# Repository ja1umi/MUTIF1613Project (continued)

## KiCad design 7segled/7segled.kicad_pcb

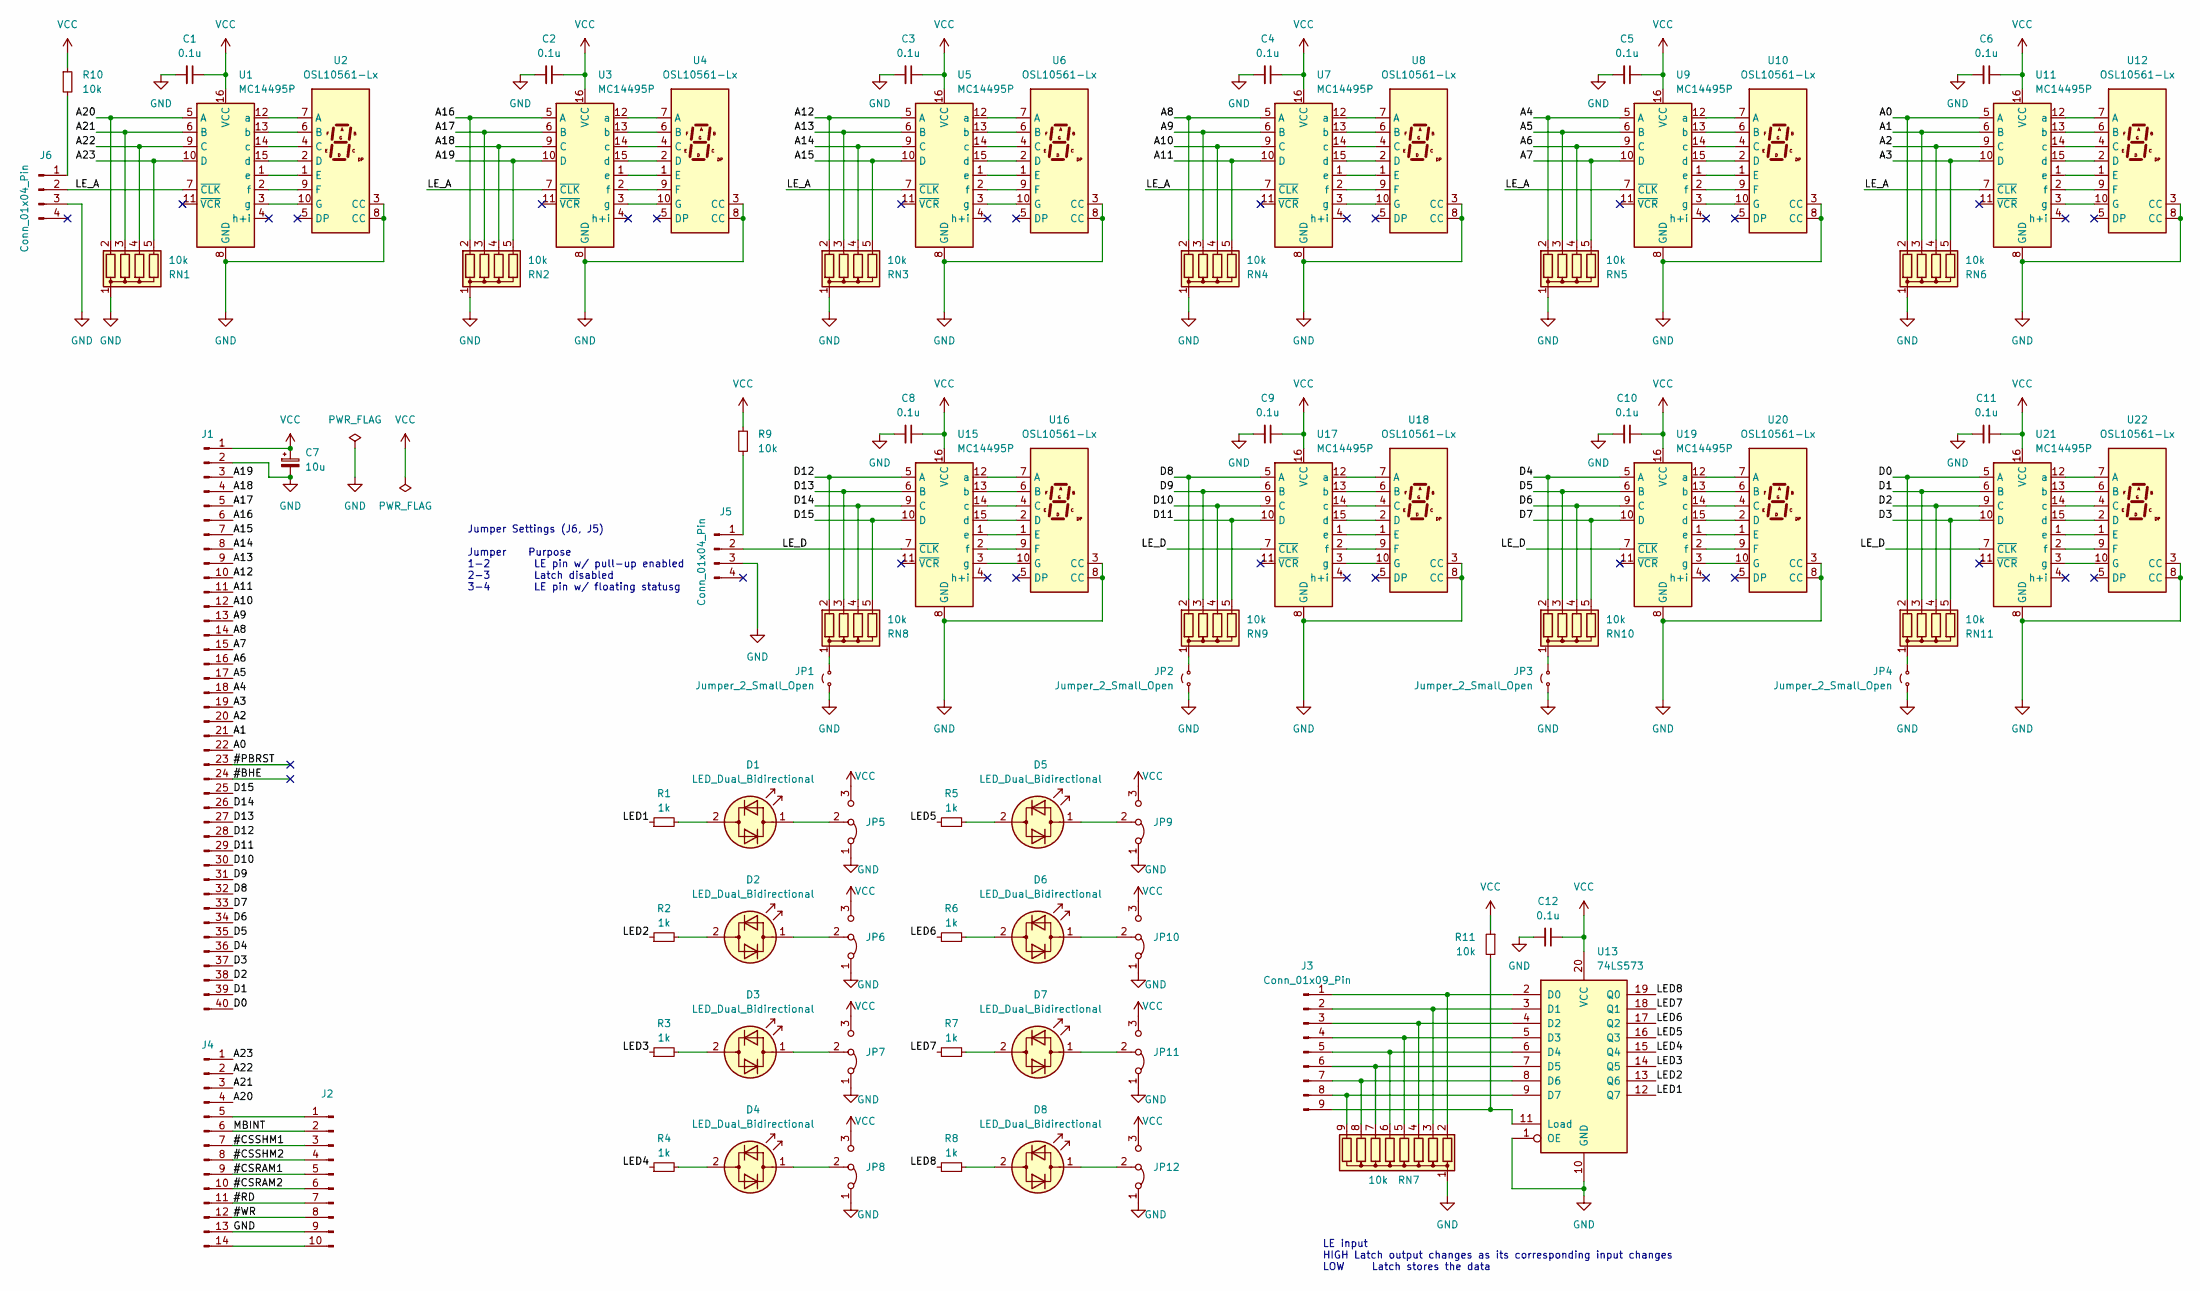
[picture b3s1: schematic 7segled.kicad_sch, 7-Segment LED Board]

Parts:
C1, C2, C3, C4, C5, C6, C8, C9, C10, C11, C12: 0.1u; C_Disc_D5.0mm_W2.5mm_P5.00mm
C7: 10u; CP_Radial_D5.0mm_P2.50mm
D1, D2, D3, D4, D5, D6, D7, D8: LED_Dual_Bidirectional; LED_D5.0mm
J1: Conn_01x40_Pin; PinHeader_1x40_P2.54mm_Vertical
J2: Conn_01x10_Pin; PinHeader_1x10_P2.54mm_Vertical
J3: Conn_01x09_Pin; PinHeader_1x09_P2.54mm_Vertical
J4: Conn_01x14_Pin; PinHeader_1x14_P2.54mm_Vertical
J5, J6: Conn_01x04_Pin; PinHeader_1x04_P2.54mm_Vertical
JP1, JP2, JP3, JP4: Jumper_2_Small_Open; PinHeader_1x02_P2.54mm_Vertical
JP5, JP6, JP7, JP8, JP9, JP10, JP11, JP12: Jumper_3_Bridged12; PinHeader_1x03_P2.54mm_Vertical
R1, R2, R3, R4, R5, R6, R7, R8: 1k; R_Axial_DIN0207_L6.3mm_D2.5mm_P7.62mm_Horizontal
R9, R10, R11: 10k; R_Axial_DIN0207_L6.3mm_D2.5mm_P7.62mm_Horizontal
RN1, RN2, RN3, RN4, RN5, RN6, RN8, RN9, RN10, RN11: 10k; R_Array_SIP5
RN7: 10k; R_Array_SIP9
U1, U3, U5, U7, U9, U11, U15, U17, U19, U21: MC14495P; DIP-16_W7.62mm_LongPads
U2, U4, U6, U8, U10, U12, U16, U18, U20, U22: OSL10561-Lx; D1X8K
U13: 74LS573; DIP-20_W7.62mm_LongPads

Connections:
/#BHE: J1.24
/#CSRAM1: J2.5, J4.9
/#CSRAM2: J2.6, J4.10
/#CSSHM1: J2.3, J4.7
/#CSSHM2: J2.4, J4.8
/#PBRST: J1.23
/#RD: J2.7, J4.11
/#WR: J2.8, J4.12
/A0: J1.22, RN6.2 (R1), U11.5 (A)
/A1: J1.21, RN6.3 (R2), U11.6 (B)
/A2: J1.20, RN6.4 (R3), U11.9 (C)
/A3: J1.19, RN6.5 (R4), U11.10 (D)
/A4: J1.18, RN5.2 (R1), U9.5 (A)
/A5: J1.17, RN5.3 (R2), U9.6 (B)
/A6: J1.16, RN5.4 (R3), U9.9 (C)
/A7: J1.15, RN5.5 (R4), U9.10 (D)
/A8: J1.14, RN4.2 (R1), U7.5 (A)
/A9: J1.13, RN4.3 (R2), U7.6 (B)
/A10: J1.12, RN4.4 (R3), U7.9 (C)
/A11: J1.11, RN4.5 (R4), U7.10 (D)
/A12: J1.10, RN3.2 (R1), U5.5 (A)
/A13: J1.9, RN3.3 (R2), U5.6 (B)
/A14: J1.8, RN3.4 (R3), U5.9 (C)
/A15: J1.7, RN3.5 (R4), U5.10 (D)
/A16: J1.6, RN2.2 (R1), U3.5 (A)
/A17: J1.5, RN2.3 (R2), U3.6 (B)
/A18: J1.4, RN2.4 (R3), U3.9 (C)
/A19: J1.3, RN2.5 (R4), U3.10 (D)
/A20: J4.4, RN1.2 (R1), U1.5 (A)
/A21: J4.3, RN1.3 (R2), U1.6 (B)
/A22: J4.2, RN1.4 (R3), U1.9 (C)
/A23: J4.1, RN1.5 (R4), U1.10 (D)
/D0: J1.40, RN11.2 (R1), U21.5 (A)
/D1: J1.39, RN11.3 (R2), U21.6 (B)
/D2: J1.38, RN11.4 (R3), U21.9 (C)
/D3: J1.37, RN11.5 (R4), U21.10 (D)
/D4: J1.36, RN10.2 (R1), U19.5 (A)
/D5: J1.35, RN10.3 (R2), U19.6 (B)
/D6: J1.34, RN10.4 (R3), U19.9 (C)
/D7: J1.33, RN10.5 (R4), U19.10 (D)
/D8: J1.32, RN9.2 (R1), U17.5 (A)
/D9: J1.31, RN9.3 (R2), U17.6 (B)
/D10: J1.30, RN9.4 (R3), U17.9 (C)
/D11: J1.29, RN9.5 (R4), U17.10 (D)
/D12: J1.28, RN8.2 (R1), U15.5 (A)
/D13: J1.27, RN8.3 (R2), U15.6 (B)
/D14: J1.26, RN8.4 (R3), U15.9 (C)
/D15: J1.25, RN8.5 (R4), U15.10 (D)
/LED1: R1.1, U13.12 (Q7)
/LED2: R2.1, U13.13 (Q6)
/LED3: R3.1, U13.14 (Q5)
/LED4: R4.1, U13.15 (Q4)
/LED5: R5.1, U13.16 (Q3)
/LED6: R6.1, U13.17 (Q2)
/LED7: R7.1, U13.18 (Q1)
/LED8: R8.1, U13.19 (Q0)
/LE_A: J6.2, U1.7 (~CLK), U3.7 (~CLK), U5.7 (~CLK), U7.7 (~CLK), U9.7 (~CLK), U11.7 (~CLK)
/LE_D: J5.2, U15.7 (~CLK), U17.7 (~CLK), U19.7 (~CLK), U21.7 (~CLK)
/MBINT: J2.2, J4.6
GND: C1.2, C2.2, C3.2, C4.2, C5.2, C6.2, C7.2, C8.2, C9.2, C10.2, C11.2, C12.2, J1.2, J2.9, J4.13, J5.3, J6.3, JP1.2 (B), JP2.2 (B), JP3.2 (B), JP4.2 (B), JP5.1 (A), JP6.1 (A), JP7.1 (A), JP8.1 (A), JP9.1 (A), JP10.1 (A), JP11.1 (A), JP12.1 (A), RN1.1 (common), RN2.1 (common), RN3.1 (common), RN4.1 (common), RN5.1 (common), RN6.1 (common), RN7.1 (common), U1.8 (GND), U2.3 (CC), U2.8 (CC), U3.8 (GND), U4.3 (CC), U4.8 (CC), U5.8 (GND), U6.3 (CC), U6.8 (CC), U7.8 (GND), U8.3 (CC), U8.8 (CC), U9.8 (GND), U10.3 (CC), U10.8 (CC), U11.8 (GND), U12.3 (CC), U12.8 (CC), U13.1 (OE), U13.10 (GND), U15.8 (GND), U16.3 (CC), U16.8 (CC), U17.8 (GND), U18.3 (CC), U18.8 (CC), U19.8 (GND), U20.3 (CC), U20.8 (CC), U21.8 (GND), U22.3 (CC), U22.8 (CC)
unnamed: D1.2 (AK), R1.2
unnamed: D1.1 (KA), JP5.2 (C)
unnamed: D2.2 (AK), R2.2
unnamed: D2.1 (KA), JP6.2 (C)
unnamed: D3.2 (AK), R3.2
unnamed: D3.1 (KA), JP7.2 (C)
unnamed: D4.2 (AK), R4.2
unnamed: D4.1 (KA), JP8.2 (C)
unnamed: D5.2 (AK), R5.2
unnamed: D5.1 (KA), JP9.2 (C)
unnamed: D6.2 (AK), R6.2
unnamed: D6.1 (KA), JP10.2 (C)
unnamed: D7.2 (AK), R7.2
unnamed: D7.1 (KA), JP11.2 (C)
unnamed: D8.2 (AK), R8.2
unnamed: D8.1 (KA), JP12.2 (C)
unnamed: J2.1, J4.5
unnamed: J2.10, J4.14
unnamed: J3.1, RN7.2 (R1), U13.2 (D0)
unnamed: J3.2, RN7.3 (R2), U13.3 (D1)
unnamed: J3.3, RN7.4 (R3), U13.4 (D2)
unnamed: J3.4, RN7.5 (R4), U13.5 (D3)
unnamed: J3.5, RN7.6 (R5), U13.6 (D4)
unnamed: J3.6, RN7.7 (R6), U13.7 (D5)
unnamed: J3.7, RN7.8 (R7), U13.8 (D6)
unnamed: J3.8, RN7.9 (R8), U13.9 (D7)
unnamed: J3.9, R11.2, U13.11 (Load)
unnamed: J5.1, R9.2
unnamed: J6.1, R10.2
unnamed: JP1.1 (A), RN8.1 (common)
unnamed: JP2.1 (A), RN9.1 (common)
unnamed: JP3.1 (A), RN10.1 (common)
unnamed: JP4.1 (A), RN11.1 (common)
unnamed: U1.12 (a), U2.7 (A)
unnamed: U1.13 (b), U2.6 (B)
unnamed: U1.14 (c), U2.4 (C)
unnamed: U1.15 (d), U2.2 (D)
unnamed: U1.1 (e), U2.1 (E)
unnamed: U1.2 (f), U2.9 (F)
unnamed: U1.3 (g), U2.10 (G)
unnamed: U3.12 (a), U4.7 (A)
unnamed: U3.13 (b), U4.6 (B)
unnamed: U3.14 (c), U4.4 (C)
unnamed: U3.15 (d), U4.2 (D)
unnamed: U3.1 (e), U4.1 (E)
unnamed: U3.2 (f), U4.9 (F)
unnamed: U3.3 (g), U4.10 (G)
unnamed: U5.12 (a), U6.7 (A)
unnamed: U5.13 (b), U6.6 (B)
unnamed: U5.14 (c), U6.4 (C)
unnamed: U5.15 (d), U6.2 (D)
unnamed: U5.1 (e), U6.1 (E)
unnamed: U5.2 (f), U6.9 (F)
unnamed: U5.3 (g), U6.10 (G)
unnamed: U7.12 (a), U8.7 (A)
unnamed: U7.13 (b), U8.6 (B)
unnamed: U7.14 (c), U8.4 (C)
unnamed: U7.15 (d), U8.2 (D)
unnamed: U7.1 (e), U8.1 (E)
unnamed: U7.2 (f), U8.9 (F)
unnamed: U7.3 (g), U8.10 (G)
unnamed: U9.12 (a), U10.7 (A)
unnamed: U9.13 (b), U10.6 (B)
unnamed: U9.14 (c), U10.4 (C)
unnamed: U9.15 (d), U10.2 (D)
unnamed: U9.1 (e), U10.1 (E)
unnamed: U9.2 (f), U10.9 (F)
unnamed: U9.3 (g), U10.10 (G)
unnamed: U11.12 (a), U12.7 (A)
unnamed: U11.13 (b), U12.6 (B)
unnamed: U11.14 (c), U12.4 (C)
unnamed: U11.15 (d), U12.2 (D)
unnamed: U11.1 (e), U12.1 (E)
unnamed: U11.2 (f), U12.9 (F)
unnamed: U11.3 (g), U12.10 (G)
unnamed: U15.12 (a), U16.7 (A)
unnamed: U15.13 (b), U16.6 (B)
unnamed: U15.14 (c), U16.4 (C)
unnamed: U15.15 (d), U16.2 (D)
unnamed: U15.1 (e), U16.1 (E)
unnamed: U15.2 (f), U16.9 (F)
unnamed: U15.3 (g), U16.10 (G)
unnamed: U17.12 (a), U18.7 (A)
unnamed: U17.13 (b), U18.6 (B)
unnamed: U17.14 (c), U18.4 (C)
unnamed: U17.15 (d), U18.2 (D)
unnamed: U17.1 (e), U18.1 (E)
unnamed: U17.2 (f), U18.9 (F)
unnamed: U17.3 (g), U18.10 (G)
unnamed: U19.12 (a), U20.7 (A)
unnamed: U19.13 (b), U20.6 (B)
unnamed: U19.14 (c), U20.4 (C)
unnamed: U19.15 (d), U20.2 (D)
unnamed: U19.1 (e), U20.1 (E)
unnamed: U19.2 (f), U20.9 (F)
unnamed: U19.3 (g), U20.10 (G)
unnamed: U21.12 (a), U22.7 (A)
unnamed: U21.13 (b), U22.6 (B)
unnamed: U21.14 (c), U22.4 (C)
unnamed: U21.15 (d), U22.2 (D)
unnamed: U21.1 (e), U22.1 (E)
unnamed: U21.2 (f), U22.9 (F)
unnamed: U21.3 (g), U22.10 (G)
VCC: C1.1, C2.1, C3.1, C4.1, C5.1, C6.1, C7.1, C8.1, C9.1, C10.1, C11.1, C12.1, J1.1, JP5.3 (B), JP6.3 (B), JP7.3 (B), JP8.3 (B), JP9.3 (B), JP10.3 (B), JP11.3 (B), JP12.3 (B), R9.1, R10.1, R11.1, U1.16 (VCC), U3.16 (VCC), U5.16 (VCC), U7.16 (VCC), U9.16 (VCC), U11.16 (VCC), U13.20 (VCC), U15.16 (VCC), U17.16 (VCC), U19.16 (VCC), U21.16 (VCC)

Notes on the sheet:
Jumper Settings (J6, J5) Jumper Purpose 1-2 LE pin w/ pull-up enabled 2-3 Latch disabled 3-4 LE pin w/ floating statusg
LE input HIGH Latch output changes as its corresponding input changes LOW Latch stores the data

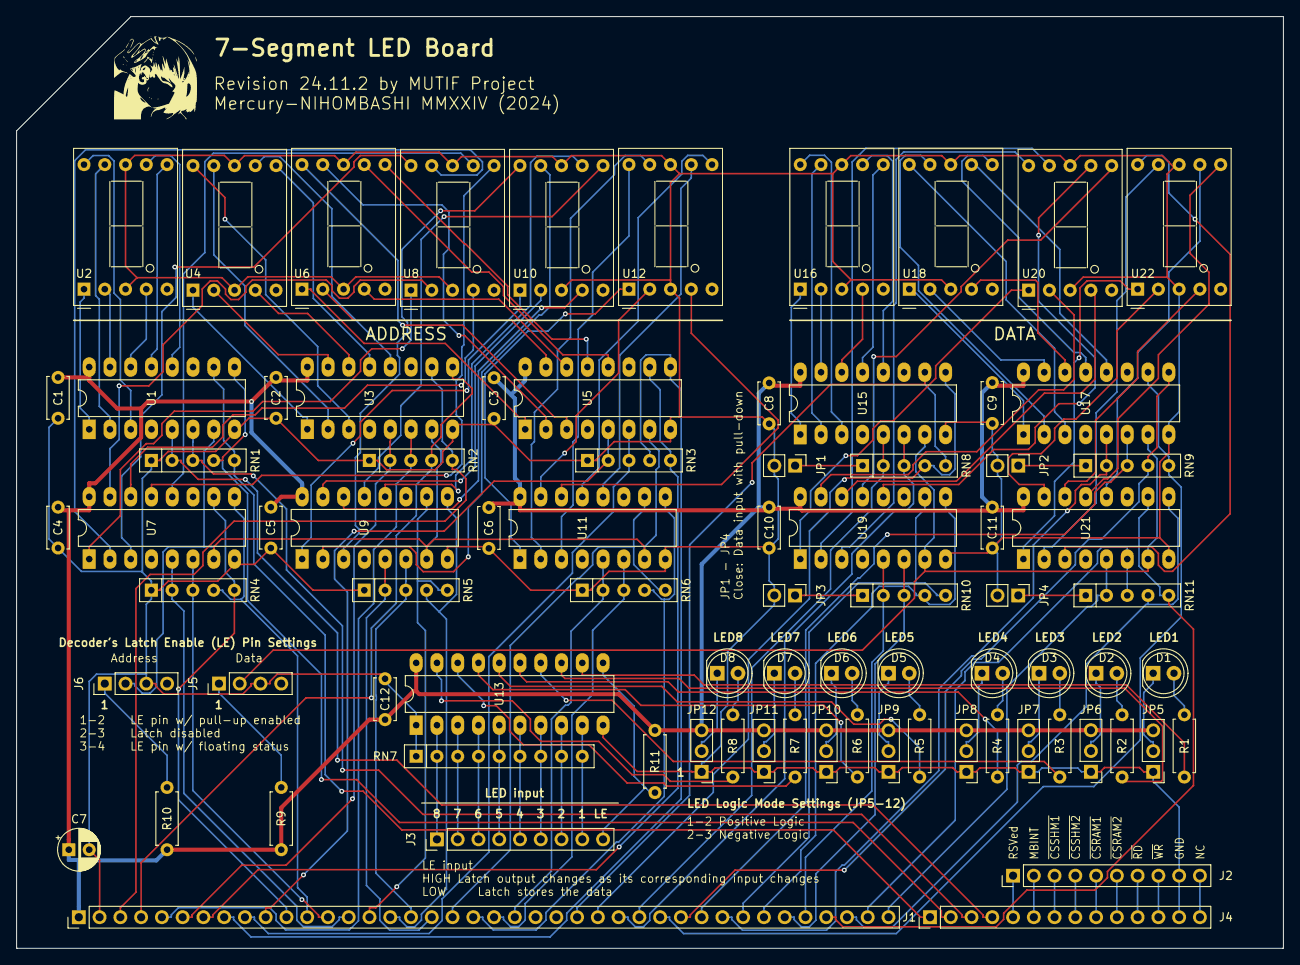
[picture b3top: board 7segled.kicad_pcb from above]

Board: 2 copper layers, 155.0 x 114.0 mm, 81 parts (0 on the bottom side), 162 nets.

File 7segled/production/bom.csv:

Designator,Footprint,Quantity,Value,LCSC Part #
"C1, C10, C11, C12, C2, C3, C4, C5, C6, C8, C9",C_Disc_D5.0mm_W2.5mm_P5.00mm,11,0.1u,
C7,CP_Radial_D5.0mm_P2.50mm,1,10u,
"D1, D2, D3, D4, D5, D6, D7, D8",LED_D5.0mm,8,LED_Dual_Bidirectional,
J1,PinHeader_1x40_P2.54mm_Vertical,1,Conn_01x40_Pin,
J2,PinHeader_1x10_P2.54mm_Vertical,1,Conn_01x10_Pin,
J3,PinHeader_1x09_P2.54mm_Vertical,1,Conn_01x09_Pin,
J4,PinHeader_1x14_P2.54mm_Vertical,1,Conn_01x14_Pin,
"J5, J6",PinHeader_1x03_P2.54mm_Vertical,2,Conn_01x03_Pin,
"JP1, JP2",PinHeader_1x02_P2.54mm_Vertical,2,Jumper_2_Small_Open,
"R1, R2, R3, R4, R5, R6, R7, R8",R_Axial_DIN0207_L6.3mm_D2.5mm_P7.62mm_Horizontal,8,1k,
"R10, R11, R9",R_Axial_DIN0207_L6.3mm_D2.5mm_P7.62mm_Horizontal,3,10k,
"RN1, RN10, RN11, RN2, RN3, RN4, RN5, RN6, RN8, RN9",R_Array_SIP5,10,10k,
"U1, U11, U15, U17, U19, U21, U3, U5, U7, U9",DIP-16_W7.62mm_LongPads,10,MC14495P,
"U10, U12, U16, U18, U2, U20, U22, U4, U6, U8",D1X8K,10,OSL10561-Lx,
U13,DIP-20_W7.62mm_LongPads,1,74LS573,

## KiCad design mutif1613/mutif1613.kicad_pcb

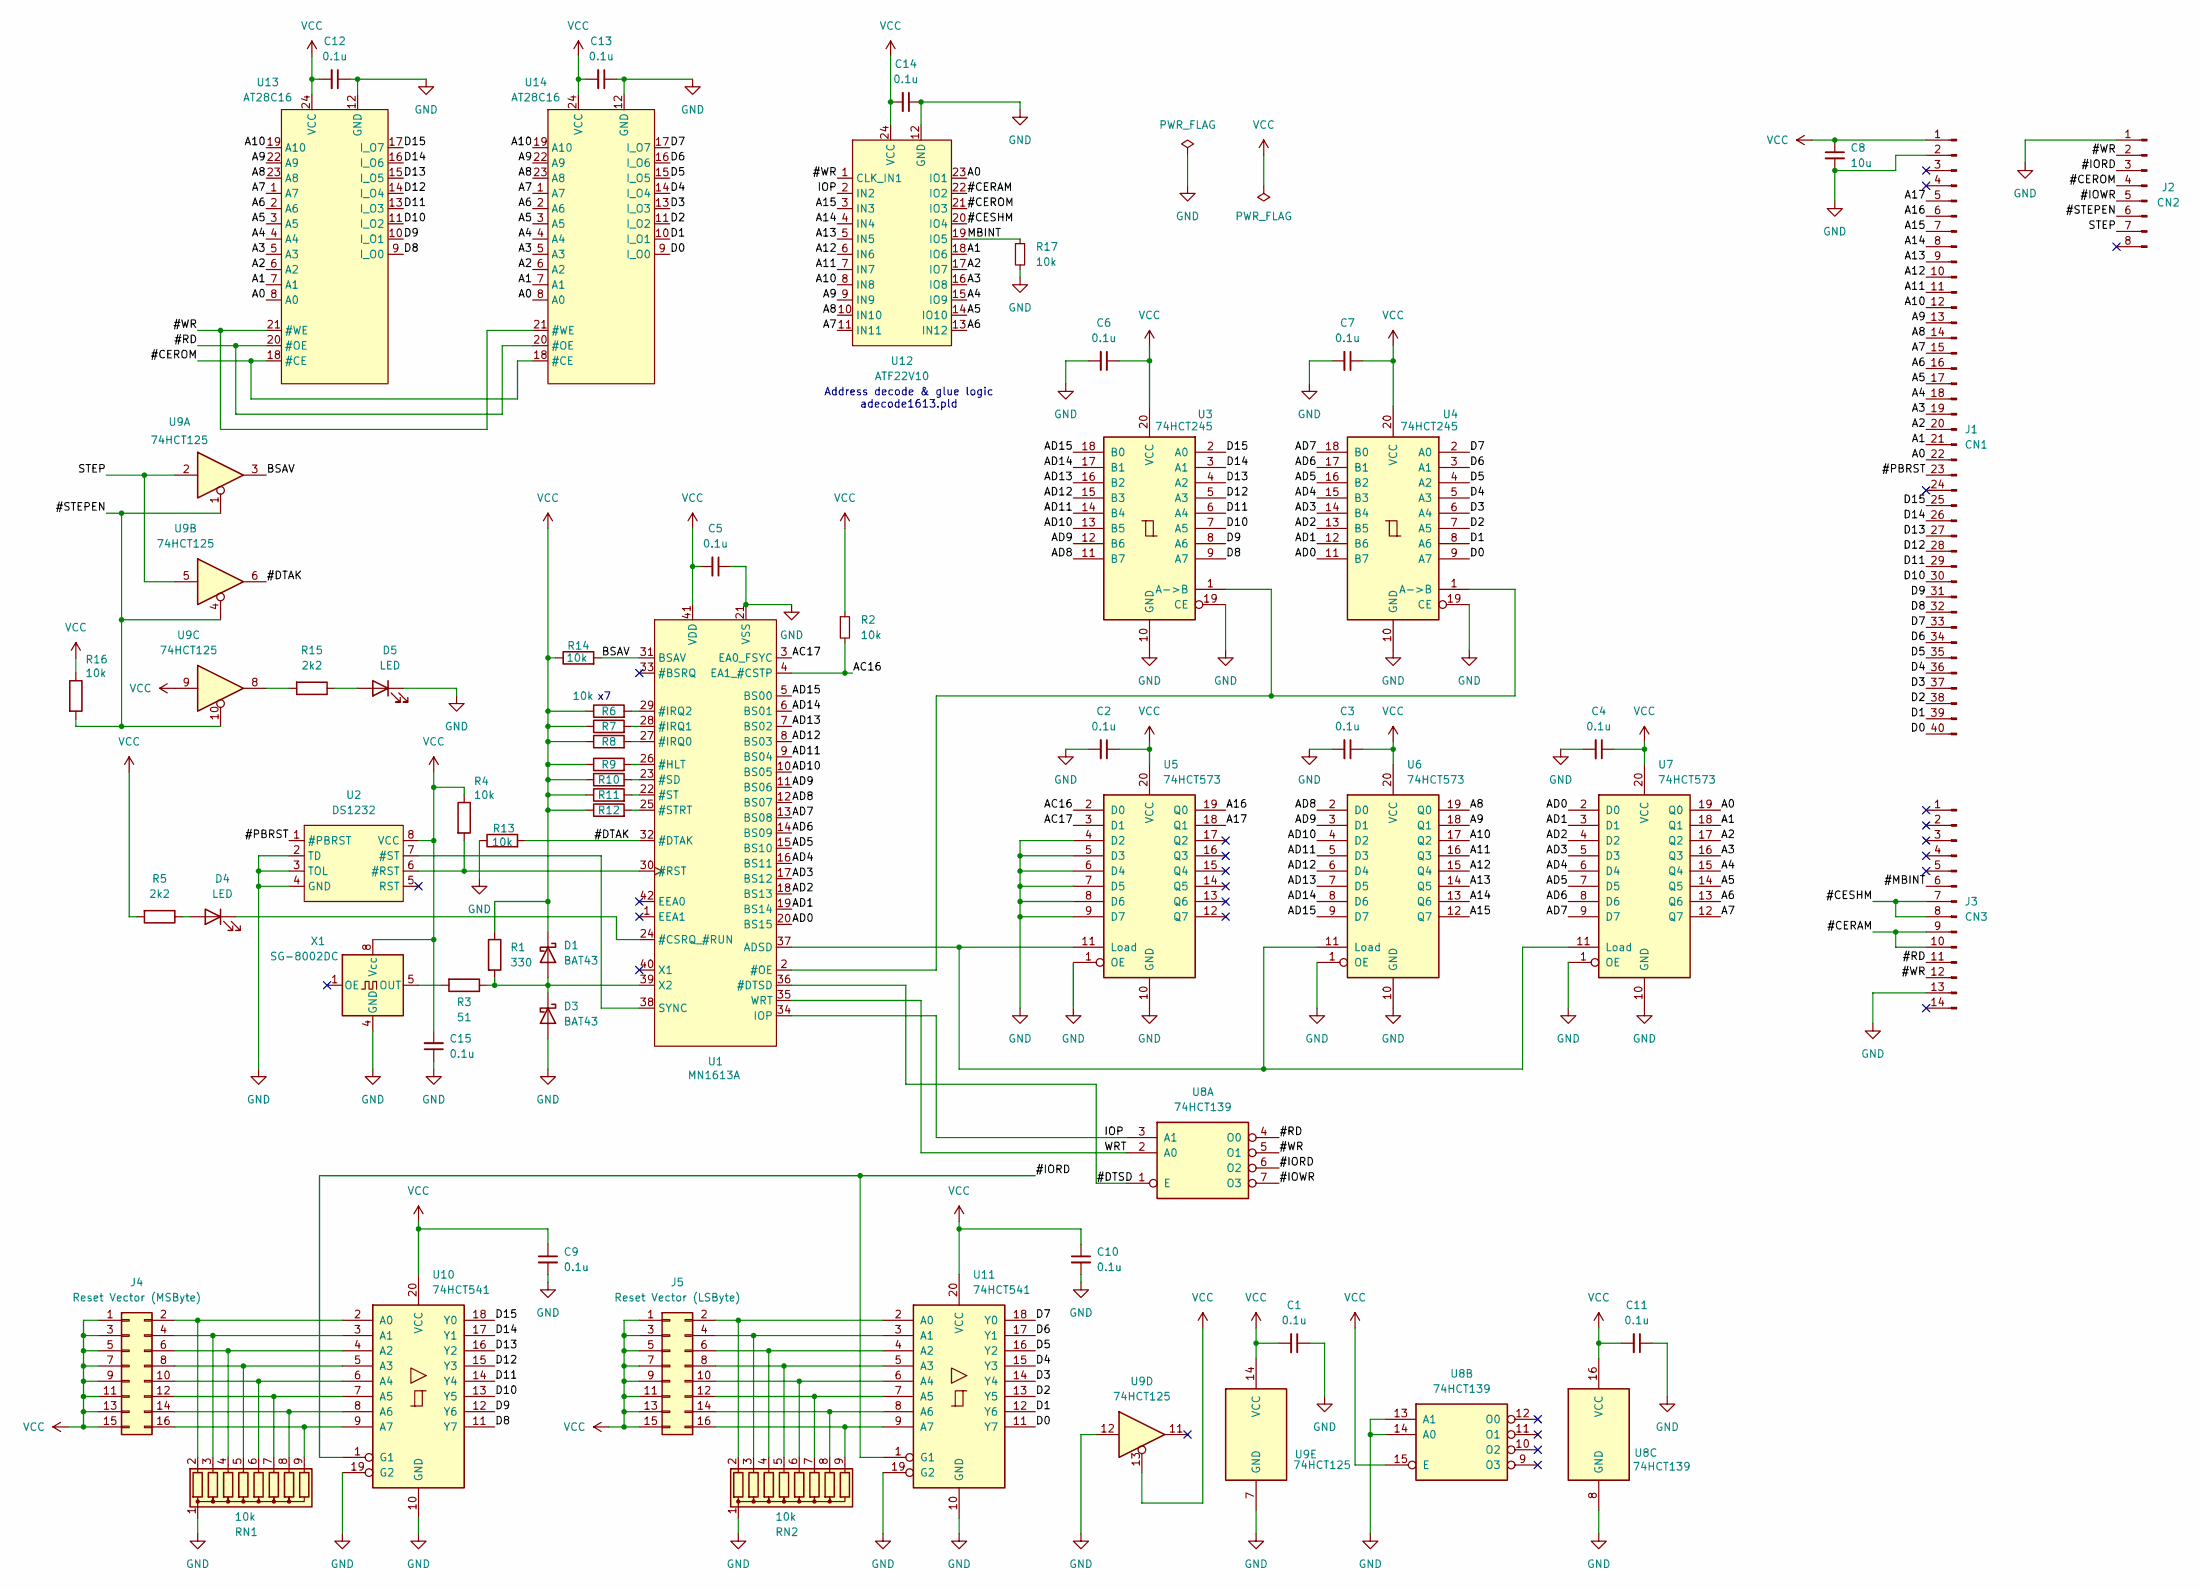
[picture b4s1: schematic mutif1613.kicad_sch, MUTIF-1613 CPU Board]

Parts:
C1, C2, C3, C4, C5, C6, C7, C9, C10, C11, C12, C13, C14, C15: 0.1u; C_Disc_D5.0mm_W2.5mm_P5.00mm
C8: 10u; CP_Radial_D5.0mm_P2.50mm
D1, D3: BAT43; D_DO-35_SOD27_P7.62mm_Horizontal
D4, D5: LED; LED_D3.0mm
J1: CN1; PinHeader_1x40_P2.54mm_Vertical
J2: CN2; PinHeader_1x08_P2.54mm_Vertical
J3: CN3; PinHeader_1x14_P2.54mm_Vertical
J4: Reset Vector (MSByte); PinHeader_2x08_P2.54mm_Vertical
J5: Reset Vector (LSByte); PinHeader_2x08_P2.54mm_Vertical
R1: 330; R_Axial_DIN0204_L3.6mm_D1.6mm_P7.62mm_Horizontal
R2, R4, R6, R7, R8, R9, R10, R11, R12, R13, R14, R16, R17: 10k; R_Axial_DIN0207_L6.3mm_D2.5mm_P7.62mm_Horizontal
R3: 51; R_Axial_DIN0207_L6.3mm_D2.5mm_P7.62mm_Horizontal
R5, R15: 2k2; R_Axial_DIN0207_L6.3mm_D2.5mm_P7.62mm_Horizontal
RN1, RN2: 10k; R_Array_SIP9
U1: MN1613A; DIP-42_W15.24mm_LongPads
U2: DS1232; DIP-8_W7.62mm_LongPads
U3, U4: 74HCT245; DIP-20_W7.62mm_LongPads
U5, U6, U7: 74HCT573; DIP-20_W7.62mm_LongPads
U8: 74HCT139; DIP-16_W7.62mm_LongPads
U9: 74HCT125; DIP-14_W7.62mm_LongPads
U10, U11: 74HCT541; DIP-20_W7.62mm_LongPads
U12: ATF22V10; DIP-24_W7.62mm_LongPads
U13, U14: AT28C16; DIP-24_W15.24mm_LongPads
X1: SG-8002DC; Oscillator_SeikoEpson_SG-8002DC

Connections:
/#CERAM: J3.9, J3.10, U12.22 (IO2)
/#CEROM: J2.4, U12.21 (IO3), U13.18 (#CE), U14.18 (#CE)
/#CESHM: J3.7, J3.8, U12.20 (IO4)
/#DTAK: R13.2, U1.32 (#DTAK), U9.6
/#DTSD: U1.36 (#DTSD), U8.1 (E)
/#IORD: J2.3, U8.6 (O2), U10.1 (G1), U11.1 (G1)
/#IOWR: J2.5, U8.7 (O3)
/#PBRST: J1.23, U2.1 (#PBRST)
/#RD: J3.11, U8.4 (O0), U13.20 (#OE), U14.20 (#OE)
/#STEPEN: J2.6, R16.2, U9.1, U9.4, U9.10
/#WR: J2.2, J3.12, U8.5 (O1), U12.1 (CLK_IN1), U13.21 (#WE), U14.21 (#WE)
/A0: J1.22, U7.19 (Q0), U12.23 (IO1), U13.8 (A0), U14.8 (A0)
/A1: J1.21, U7.18 (Q1), U12.18 (IO6), U13.7 (A1), U14.7 (A1)
/A2: J1.20, U7.17 (Q2), U12.17 (IO7), U13.6 (A2), U14.6 (A2)
/A3: J1.19, U7.16 (Q3), U12.16 (IO8), U13.5 (A3), U14.5 (A3)
/A4: J1.18, U7.15 (Q4), U12.15 (IO9), U13.4 (A4), U14.4 (A4)
/A5: J1.17, U7.14 (Q5), U12.14 (IO10), U13.3 (A5), U14.3 (A5)
/A6: J1.16, U7.13 (Q6), U12.13 (IN12), U13.2 (A6), U14.2 (A6)
/A7: J1.15, U7.12 (Q7), U12.11 (IN11), U13.1 (A7), U14.1 (A7)
/A8: J1.14, U6.19 (Q0), U12.10 (IN10), U13.23 (A8), U14.23 (A8)
/A9: J1.13, U6.18 (Q1), U12.9 (IN9), U13.22 (A9), U14.22 (A9)
/A10: J1.12, U6.17 (Q2), U12.8 (IN8), U13.19 (A10), U14.19 (A10)
/A11: J1.11, U6.16 (Q3), U12.7 (IN7)
/A12: J1.10, U6.15 (Q4), U12.6 (IN6)
/A13: J1.9, U6.14 (Q5), U12.5 (IN5)
/A14: J1.8, U6.13 (Q6), U12.4 (IN4)
/A15: J1.7, U6.12 (Q7), U12.3 (IN3)
/A16: J1.6, U5.19 (Q0)
/A17: J1.5, U5.18 (Q1)
/AC16: R2.2, U1.4 (EA1_#CSTP), U5.2 (D0)
/AC17: U1.3 (EA0_FSYC), U5.3 (D1)
/AD0: U1.20 (BS15), U4.11 (B7), U7.2 (D0)
/AD1: U1.19 (BS14), U4.12 (B6), U7.3 (D1)
/AD2: U1.18 (BS13), U4.13 (B5), U7.4 (D2)
/AD3: U1.17 (BS12), U4.14 (B4), U7.5 (D3)
/AD4: U1.16 (BS11), U4.15 (B3), U7.6 (D4)
/AD5: U1.15 (BS10), U4.16 (B2), U7.7 (D5)
/AD6: U1.14 (BS09), U4.17 (B1), U7.8 (D6)
/AD7: U1.13 (BS08), U4.18 (B0), U7.9 (D7)
/AD8: U1.12 (BS07), U3.11 (B7), U6.2 (D0)
/AD9: U1.11 (BS06), U3.12 (B6), U6.3 (D1)
/AD10: U1.10 (BS05), U3.13 (B5), U6.4 (D2)
/AD11: U1.9 (BS04), U3.14 (B4), U6.5 (D3)
/AD12: U1.8 (BS03), U3.15 (B3), U6.6 (D4)
/AD13: U1.7 (BS02), U3.16 (B2), U6.7 (D5)
/AD14: U1.6 (BS01), U3.17 (B1), U6.8 (D6)
/AD15: U1.5 (BS00), U3.18 (B0), U6.9 (D7)
/BSAV: R14.2, U1.31 (BSAV), U9.3
/D0: J1.40, U4.9 (A7), U11.11 (Y7), U14.9 (I_O0)
/D1: J1.39, U4.8 (A6), U11.12 (Y6), U14.10 (I_O1)
/D2: J1.38, U4.7 (A5), U11.13 (Y5), U14.11 (I_O2)
/D3: J1.37, U4.6 (A4), U11.14 (Y4), U14.13 (I_O3)
/D4: J1.36, U4.5 (A3), U11.15 (Y3), U14.14 (I_O4)
/D5: J1.35, U4.4 (A2), U11.16 (Y2), U14.15 (I_O5)
/D6: J1.34, U4.3 (A1), U11.17 (Y1), U14.16 (I_O6)
/D7: J1.33, U4.2 (A0), U11.18 (Y0), U14.17 (I_O7)
/D8: J1.32, U3.9 (A7), U10.11 (Y7), U13.9 (I_O0)
/D9: J1.31, U3.8 (A6), U10.12 (Y6), U13.10 (I_O1)
/D10: J1.30, U3.7 (A5), U10.13 (Y5), U13.11 (I_O2)
/D11: J1.29, U3.6 (A4), U10.14 (Y4), U13.13 (I_O3)
/D12: J1.28, U3.5 (A3), U10.15 (Y3), U13.14 (I_O4)
/D13: J1.27, U3.4 (A2), U10.16 (Y2), U13.15 (I_O5)
/D14: J1.26, U3.3 (A1), U10.17 (Y1), U13.16 (I_O6)
/D15: J1.25, U3.2 (A0), U10.18 (Y0), U13.17 (I_O7)
/IOP: U1.34 (IOP), U8.3 (A1), U12.2 (IN2)
/STEP: J2.7, U9.2, U9.5
/WRT: U1.35 (WRT), U8.2 (A0)
unnamed: D1.2 (A), D3.1 (K), R1.2, R3.1, U1.39 (X2)
unnamed: D4.2 (A), R5.1
unnamed: D4.1 (K), U1.24 (#CSRQ_#RUN)
unnamed: D5.2 (A), R15.1
unnamed: J4.2, RN1.2 (R1), U10.2 (A0)
unnamed: J4.4, RN1.3 (R2), U10.3 (A1)
unnamed: J4.6, RN1.4 (R3), U10.4 (A2)
unnamed: J4.8, RN1.5 (R4), U10.5 (A3)
unnamed: J4.10, RN1.6 (R5), U10.6 (A4)
unnamed: J4.12, RN1.7 (R6), U10.7 (A5)
unnamed: J4.14, RN1.8 (R7), U10.8 (A6)
unnamed: J4.16, RN1.9 (R8), U10.9 (A7)
unnamed: J5.2, RN2.2 (R1), U11.2 (A0)
unnamed: J5.4, RN2.3 (R2), U11.3 (A1)
unnamed: J5.6, RN2.4 (R3), U11.4 (A2)
unnamed: J5.8, RN2.5 (R4), U11.5 (A3)
unnamed: J5.10, RN2.6 (R5), U11.6 (A4)
unnamed: J5.12, RN2.7 (R6), U11.7 (A5)
unnamed: J5.14, RN2.8 (R7), U11.8 (A6)
unnamed: J5.16, RN2.9 (R8), U11.9 (A7)
unnamed: R15.2, U9.8
unnamed: R9.2, U1.26 (#HLT)
unnamed: R8.2, U1.27 (#IRQ0)
unnamed: R7.2, U1.28 (#IRQ1)
unnamed: R6.2, U1.29 (#IRQ2)
unnamed: U1.2 (#OE), U3.1 (A->B), U4.1 (A->B)
unnamed: R4.2, U1.30 (#RST), U2.6 (#RST)
unnamed: R10.2, U1.23 (#SD)
unnamed: R11.2, U1.22 (#ST)
unnamed: R12.2, U1.25 (#STRT)
unnamed: U1.37 (ADSD), U5.11 (Load), U6.11 (Load), U7.11 (Load)
unnamed: U1.38 (SYNC), U2.7 (#ST)
unnamed: R3.2, X1.5 (OUT)

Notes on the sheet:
Address decode & glue logic adecode1613.pld

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
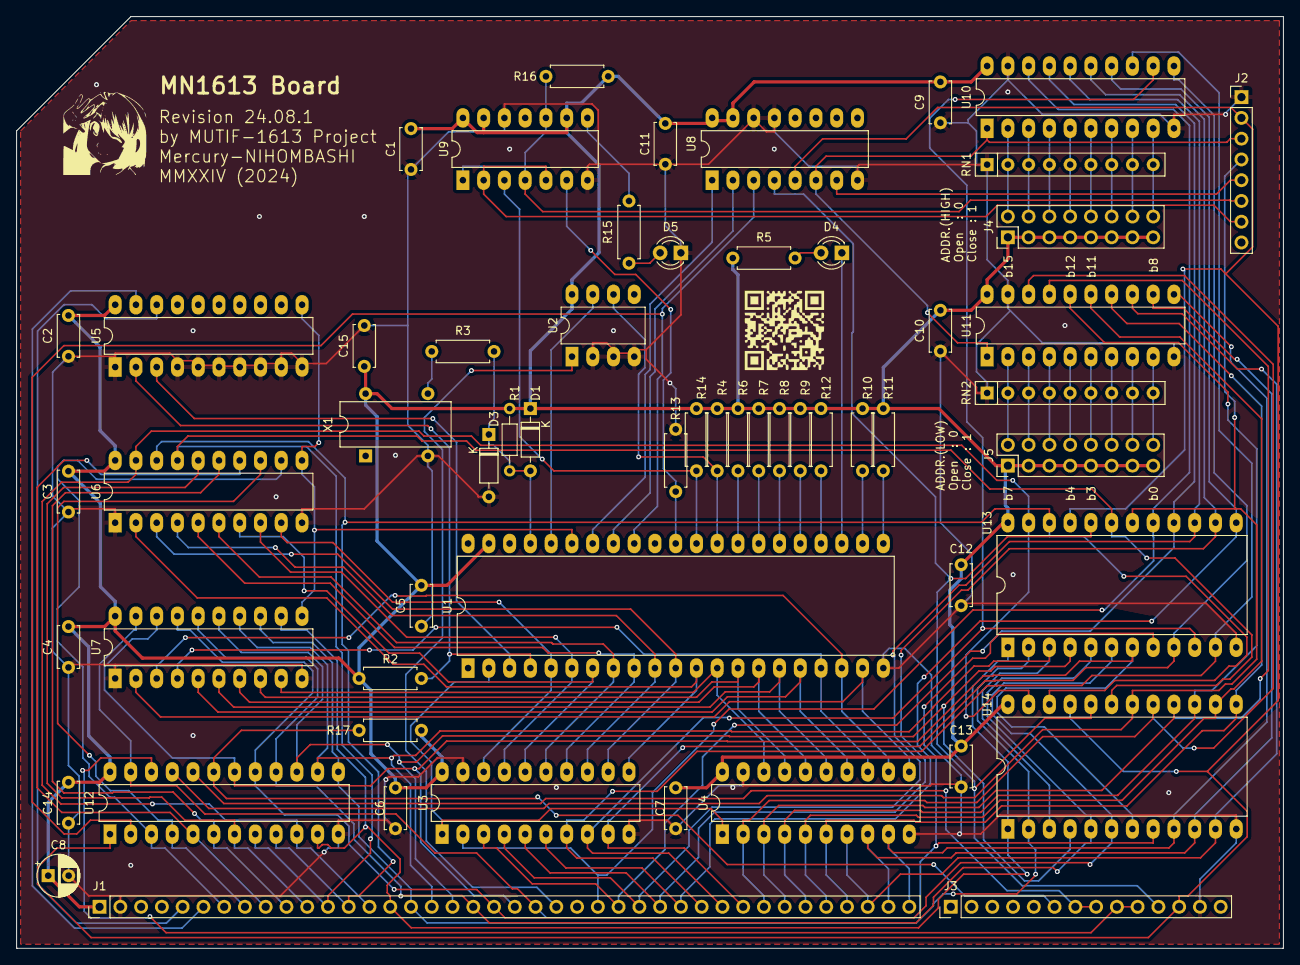
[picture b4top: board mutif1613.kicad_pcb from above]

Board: 2 copper layers, 155.0 x 114.0 mm, 60 parts (0 on the bottom side), 103 nets.

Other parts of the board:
G1: LOGO; QR_GitHub_MUTIF1613
G2: LOGO; silk_icon

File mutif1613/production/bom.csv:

Designator,Footprint,Quantity,Value,LCSC Part #
"C1, C10, C11, C12, C13, C14, C15, C2, C3, C4, C5, C6, C7, C9",C_Disc_D5.0mm_W2.5mm_P5.00mm,14,0.1u,
C8,CP_Radial_D5.0mm_P2.50mm,1,10u,
"D1, D3",D_DO-35_SOD27_P7.62mm_Horizontal,2,BAT43,
"D4, D5",LED_D3.0mm,2,LED,
J1,PinHeader_1x40_P2.54mm_Vertical,1,CN1,
J2,PinHeader_1x08_P2.54mm_Vertical,1,CN2,
J3,PinHeader_1x14_P2.54mm_Vertical,1,CN3,
J4,PinHeader_2x08_P2.54mm_Vertical,1,Reset Vector (MSByte),
J5,PinHeader_2x08_P2.54mm_Vertical,1,Reset Vector (LSByte),
R1,R_Axial_DIN0204_L3.6mm_D1.6mm_P7.62mm_Horizontal,1,330,
"R10, R11, R12, R13, R14, R16, R17, R2, R4, R6, R7, R8, R9",R_Axial_DIN0207_L6.3mm_D2.5mm_P7.62mm_Horizontal,13,10k,
"R15, R5",R_Axial_DIN0207_L6.3mm_D2.5mm_P7.62mm_Horizontal,2,2k2,
R3,R_Axial_DIN0207_L6.3mm_D2.5mm_P7.62mm_Horizontal,1,51,
"RN1, RN2",R_Array_SIP9,2,10k,
U1,DIP-42_W15.24mm_LongPads,1,MN1613A,
"U10, U11",DIP-20_W7.62mm_LongPads,2,74HCT541,
U12,DIP-24_W7.62mm_LongPads,1,ATF22V10,
"U13, U14",DIP-24_W15.24mm_LongPads,2,AT28C16,
U2,DIP-8_W7.62mm_LongPads,1,DS1232,
"U3, U4",DIP-20_W7.62mm_LongPads,2,74HCT245,
"U5, U6, U7",DIP-20_W7.62mm_LongPads,3,74HCT573,
U8,DIP-16_W7.62mm_LongPads,1,74HCT139,
U9,DIP-14_W7.62mm_LongPads,1,74HCT125,
X1,Oscillator_SeikoEpson_SG-8002DC,1,SG-8002DC,

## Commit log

2024-12-31 Added design data
2024-12-31 Removed duplicate files
2024-12-31 Removed duplicate files (EEPROM related files)
